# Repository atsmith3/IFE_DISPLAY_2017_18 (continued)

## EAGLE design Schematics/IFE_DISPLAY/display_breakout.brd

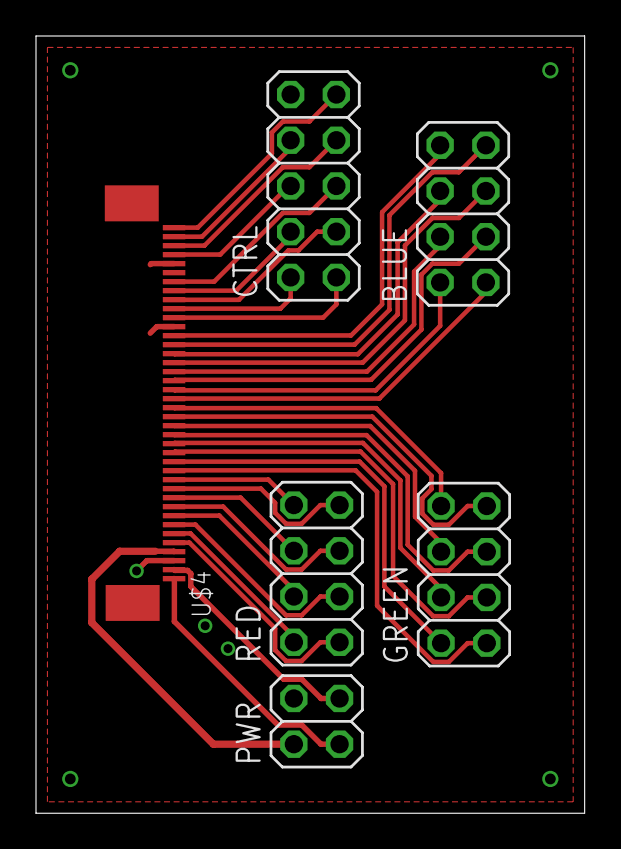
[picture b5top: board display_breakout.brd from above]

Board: 2 copper layers, 30.5 x 43.2 mm, 6 parts (0 on the bottom side), 37 nets.

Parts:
BLUE: 2X04
CTRL: 2X05
GREEN: 2X04
PWR: 2X02
RED: 2X04
U$4: ZIF40_0.5MM_PITCH; ZIF40

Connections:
+3V3: PWR.2, U$4.P$4
BLUE_0: BLUE.1, U$4.P$21
BLUE_1: BLUE.2, U$4.P$22
BLUE_2: BLUE.3, U$4.P$23
BLUE_3: BLUE.4, U$4.P$24
BLUE_4: BLUE.5, U$4.P$25
BLUE_5: BLUE.6, U$4.P$26
BLUE_6: BLUE.7, U$4.P$27
BLUE_7: BLUE.8, U$4.P$28
DISP_CLK: CTRL.1, U$4.P$30
DISP_DEN: CTRL.5, U$4.P$34
DISP_EN: CTRL.2, U$4.P$31
DISP_HSYNC: CTRL.3, U$4.P$32
DISP_LEDA: PWR.3, U$4.P$2
DISP_LEDK: PWR.1, U$4.P$1
DISP_VSYNC: CTRL.4, U$4.P$33
DISP_XL: CTRL.8, U$4.P$39
DISP_XR: CTRL.6, U$4.P$37
DISP_YD: CTRL.7, U$4.P$38
DISP_YU: CTRL.9, U$4.P$40
GND: PWR.4, U$4.P$3, U$4.P$29, U$4.P$36
GREEN_0: GREEN.1, U$4.P$13
GREEN_1: GREEN.2, U$4.P$14
GREEN_2: GREEN.3, U$4.P$15
GREEN_3: GREEN.4, U$4.P$16
GREEN_4: GREEN.5, U$4.P$17
GREEN_5: GREEN.6, U$4.P$18
GREEN_6: GREEN.7, U$4.P$19
GREEN_7: GREEN.8, U$4.P$20
RED_0: RED.1, U$4.P$5
RED_1: RED.2, U$4.P$6
RED_2: RED.3, U$4.P$7
RED_3: RED.4, U$4.P$8
RED_4: RED.5, U$4.P$9
RED_5: RED.6, U$4.P$10
RED_6: RED.7, U$4.P$11
RED_7: RED.8, U$4.P$12

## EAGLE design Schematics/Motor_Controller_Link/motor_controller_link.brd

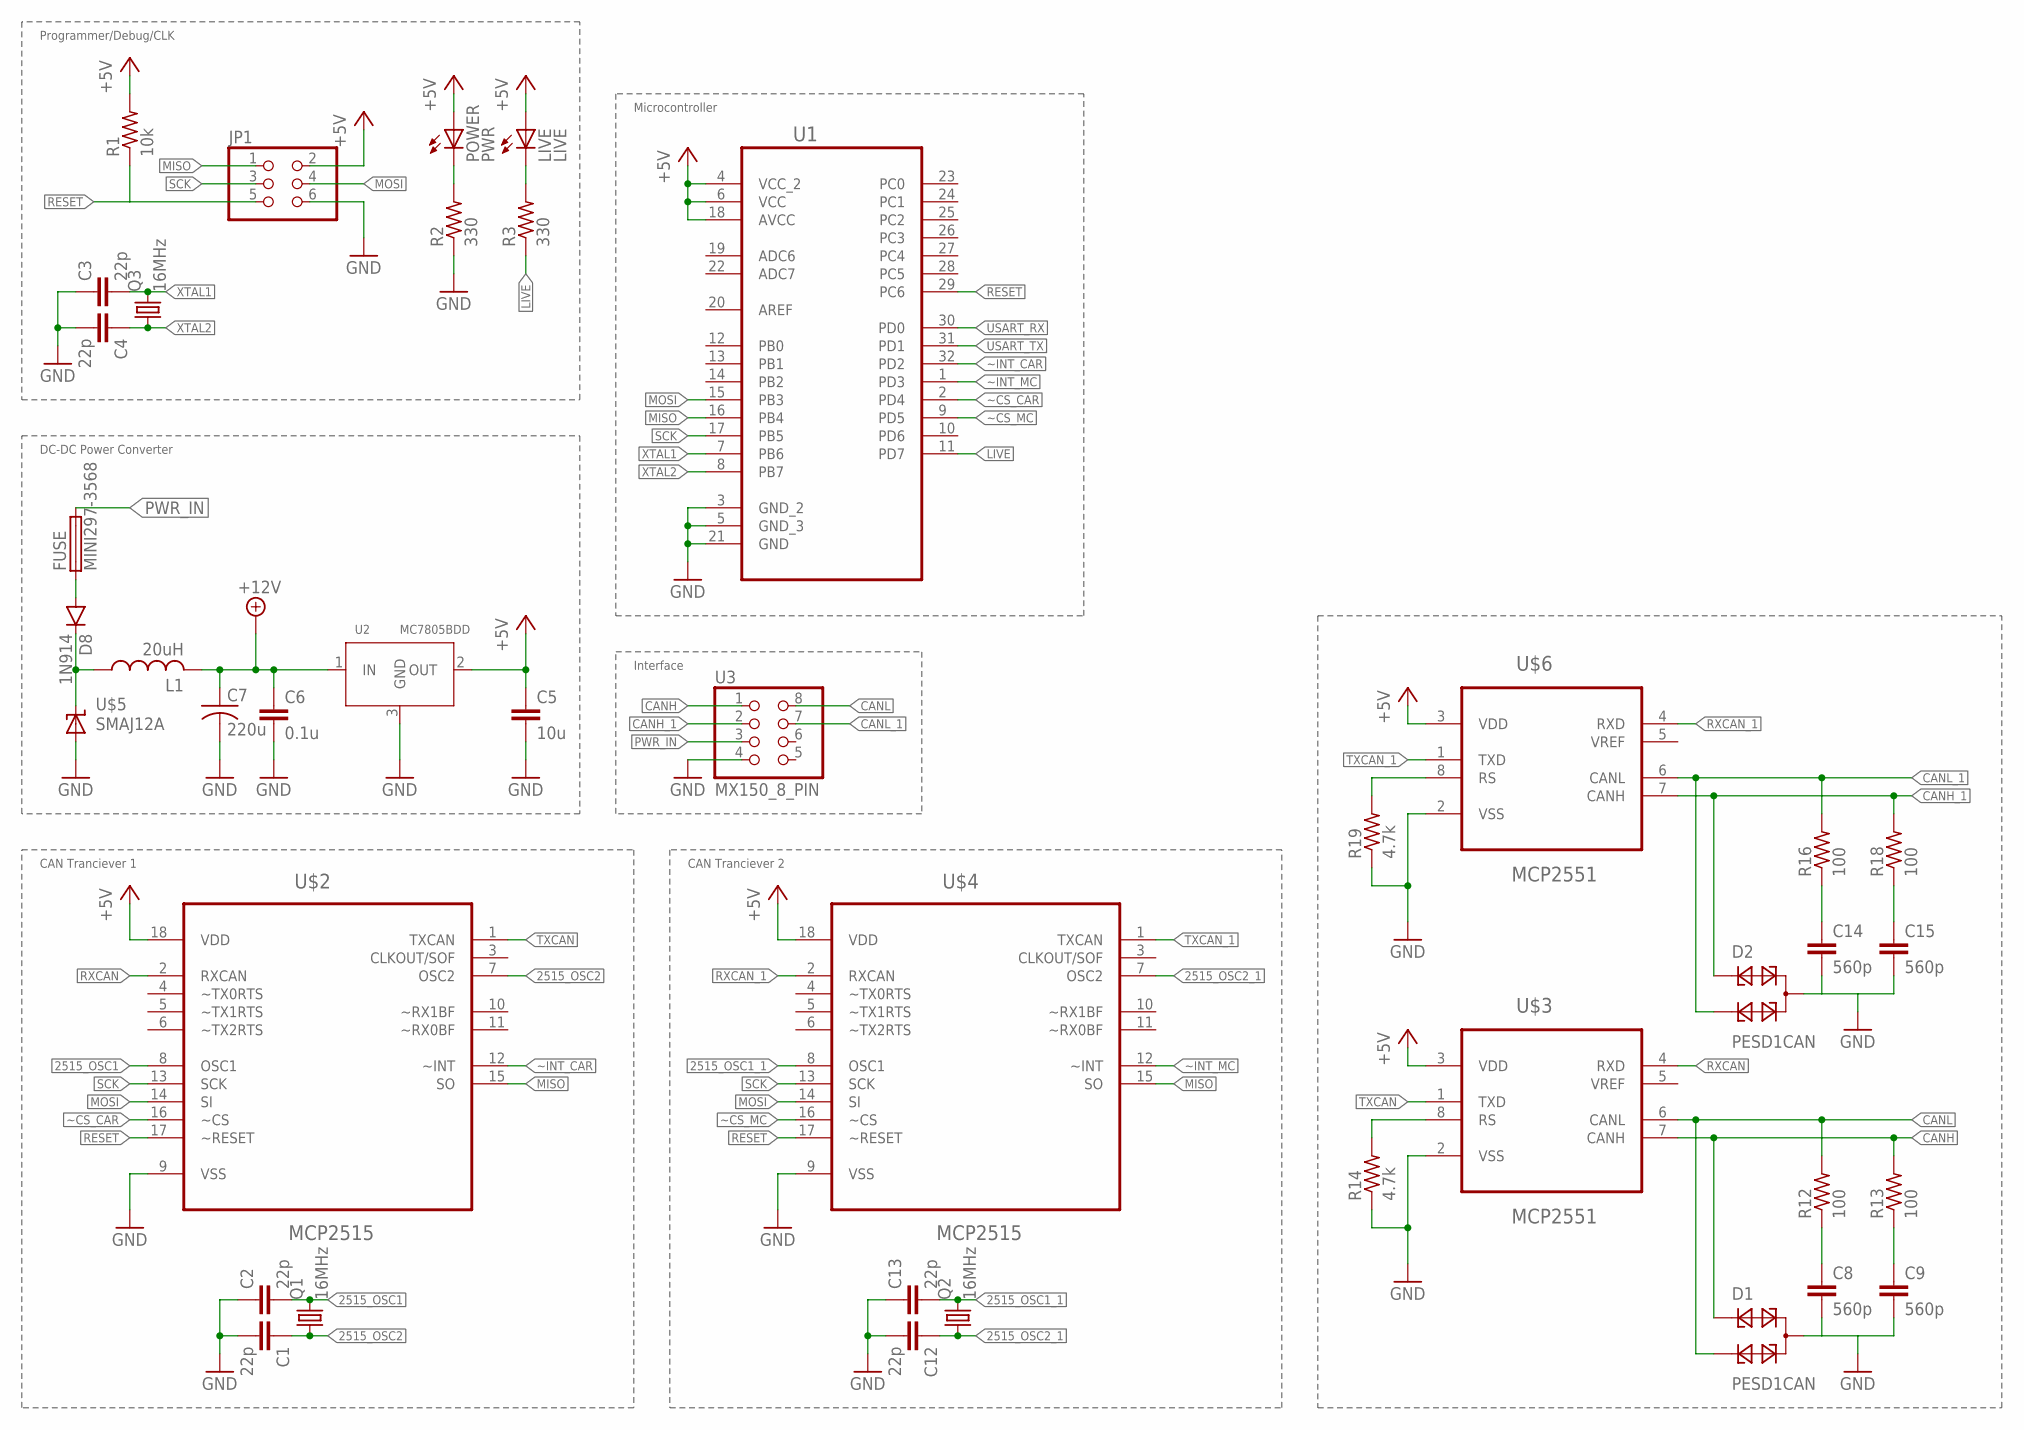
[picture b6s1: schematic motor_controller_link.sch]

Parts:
C1, C2, C3, C4, C12, C13: 22p; C0805K
C5: 10u; C0805K
C6: 0.1u; C0805K
C7: 220u; C1206
C8, C9, C14, C15: 560p; C0805K
D1, D2: PESD1CAN; SOT23
D8: 1N914; SMA-DIODE
FUSE: MINI297-3568; 3568
JP1: PINHD-2X3; 2X03
L1: 20uH; MSS7348
LIVE: LIVE; SML0805
POWER: PWR; SML0805
Q1, Q2, Q3: 16MHz; CTS406
R1: 10k; R0805
R2, R3: 330; R0805
R12, R13, R16, R18: 100; R0805
R14, R19: 4.7k; R0805
U1: ATMEGA328P-AU; QFP80P900X900X120-32N
U2: MC7805BDD; DPAK
U3: MX150_8_PIN; MX150_8
U$2, U$4: MCP2515; SOIC127P1034X264-18N
U$3, U$6: MCP2551; SOIC127P600X175-8N
U$5: SMAJ12A; DO-214AC

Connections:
2515_OSC1: C2.2, Q1.3 (2), U$2.8 (OSC1)
2515_OSC1_1: C13.2, Q2.3 (2), U$4.8 (OSC1)
2515_OSC2: C1.1, Q1.1, U$2.7 (OSC2)
2515_OSC2_1: C12.1, Q2.1, U$4.7 (OSC2)
+5V: C5.1, JP1.2, LIVE.A, POWER.A, R1.2, U1.4 (VCC_2), U1.6 (VCC), U1.18 (AVCC), U2.2 (OUT), U$2.18 (VDD), U$3.3 (VDD), U$4.18 (VDD), U$6.3 (VDD)
+12V: C6.1, C7.1, L1.P$2 (2), U2.1 (IN)
CANH: D1.1, R13.2, U3.1, U$3.7 (CANH)
CANH_1: D2.1, R18.2, U3.2 (3), U$6.7 (CANH)
CANL: D1.2, R12.2, U3.8 (2), U$3.6 (CANL)
CANL_1: D2.2, R16.2, U3.7 (4), U$6.6 (CANL)
GND: C1.2, C2.1, C3.1, C4.2, C5.2, C6.2, C7.2, C8.2, C9.2, C12.2, C13.1, C14.2, C15.2, D1.3, D2.3, JP1.6, R2.1, R14.1, R19.1, U1.3 (GND_2), U1.5 (GND_3), U1.21 (GND), U2.3 (GND), U3.4 (7), U$2.9 (VSS), U$3.2 (VSS), U$4.9 (VSS), U$5.A, U$6.2 (VSS)
LIVE: R3.1, U1.11 (PD7)
MISO: JP1.1, U1.16 (PB4), U$2.15 (SO), U$4.15 (SO)
MOSI: JP1.4, U1.15 (PB3), U$2.14 (SI), U$4.14 (SI)
unnamed: R14.2, U$3.8 (RS)
unnamed: C14.1, R16.1
unnamed: POWER.C, R2.2
unnamed: LIVE.C, R3.2
unnamed: C8.1, R12.1
unnamed: C9.1, R13.1
unnamed: C15.1, R18.1
unnamed: D8.C, L1.P$1 (1), U$5.C
unnamed: R19.2, U$6.8 (RS)
unnamed: D8.A, FUSE.P$1 (1), FUSE.P$4 (1)
PWR_IN: FUSE.P$2 (2), FUSE.P$3 (2), U3.3 (5)
RESET: JP1.5, R1.1, U1.29 (PC6), U$2.17 (~RESET), U$4.17 (~RESET)
RXCAN: U$2.2 (RXCAN), U$3.4 (RXD)
RXCAN_1: U$4.2 (RXCAN), U$6.4 (RXD)
SCK: JP1.3, U1.17 (PB5), U$2.13 (SCK), U$4.13 (SCK)
TXCAN: U$2.1 (TXCAN), U$3.1 (TXD)
TXCAN_1: U$4.1 (TXCAN), U$6.1 (TXD)
USART_RX: U1.30 (PD0)
USART_TX: U1.31 (PD1)
XTAL1: C3.2, Q3.3 (2), U1.7 (PB6)
XTAL2: C4.1, Q3.1, U1.8 (PB7)
~CS_CAR: U1.2 (PD4), U$2.16 (~CS)
~CS_MC: U1.9 (PD5), U$4.16 (~CS)
~INT_CAR: U1.32 (PD2), U$2.12 (~INT)
~INT_MC: U1.1 (PD3), U$4.12 (~INT)

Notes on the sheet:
DC-DC Power Converter
CAN Tranciever 1
CAN Tranciever 2
Programmer/Debug/CLK
Microcontroller
Interface

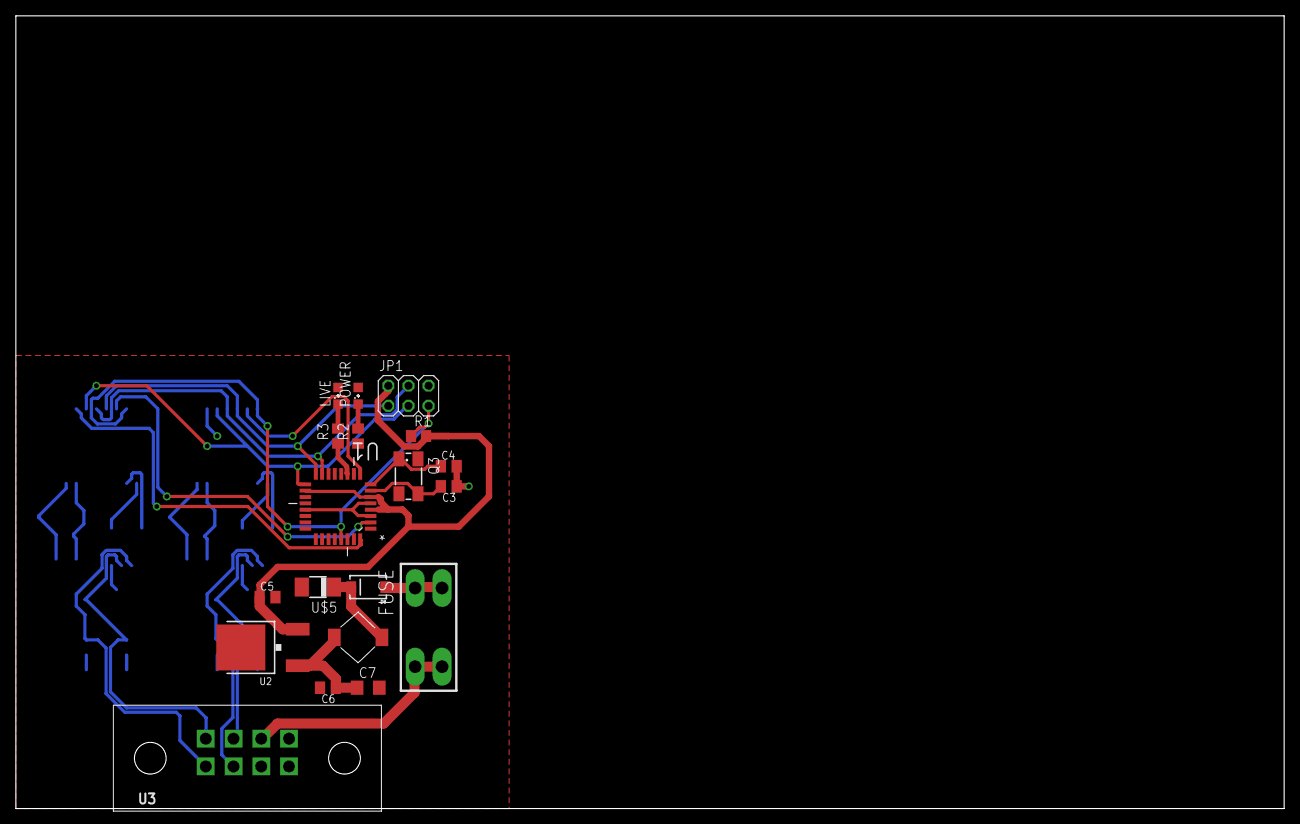
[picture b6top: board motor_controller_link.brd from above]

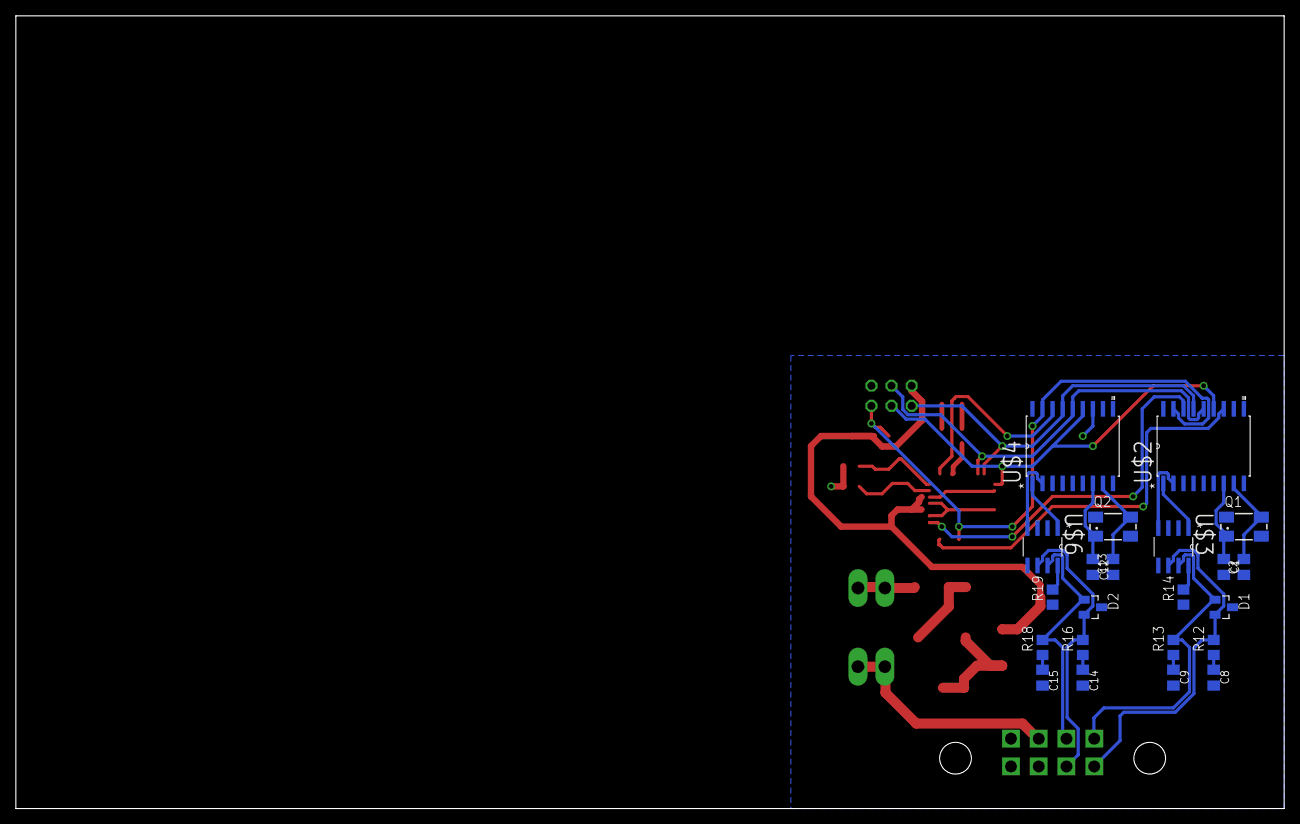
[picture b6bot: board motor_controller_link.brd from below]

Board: 2 copper layers, 160.0 x 100.0 mm, 41 parts (22 on the bottom side), 37 nets.

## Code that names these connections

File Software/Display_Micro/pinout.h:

/*
 * Illini Formula Electric
 * 
 * Dashboard Revision 2 - 2018
 *
 * Pinout
 *
 */

#ifndef _PINOUT_H
#define _PINOUT_H

#define MOSI                        11
#define MISO                        12
#define SCK                         13
#define RXD                         0
#define TXD                         1     
#define CS_CAN                      19    // Chip Select for CAN Module
#define INT_CAN                     2     // Interrupt pin for CAN Module
#define DISPLAY_PWM                 9
#define DEBUG                       10    // Debug LED
//#define CAN_STBY                  9     // CAN Sleep Mode Select (MCP 25625)

/* FPGA INTERFACE */
#define FPGA_D0                     14
#define FPGA_D1                     15
#define FPGA_D2                     16
#define FPGA_D3                     17
#define FPGA_R0                     4
#define FPGA_R1                     5
#define FPGA_R2                     6
#define FPGA_R3                     7
#define FPGA_WRITE                  3
#define FPGA_ADDR                   18

#endif

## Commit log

2017-06-30 Organization
2017-06-30 Adding documentation
2017-06-30 Design Changes
2017-07-07 base FPGA project added
2017-09-08 Finished bootloader circuitry for Cyclone II
2017-09-08 Added Micro programmer circuit
2017-09-15 Updated the Display Design Specification
2017-09-28 Starting Layout of Motor Controller Interface
2017-09-28 Adding projects
2017-09-28 Almost done with initial layout
2017-10-08 More work on Display Schematic
2017-10-09 Figuring out power circuit
2017-10-10 More progress on the schematic
2017-10-15 Started creating the ZIF 40 Pin Connector
2017-10-15 Working on Breakout Board Layout
2017-10-15 Display Breakout Board done
2017-10-16 figuring out DC-DC converters
2017-10-28 DCDC added need to adjust values
2017-10-31 Finalizing Display Schematic
2017-10-31 Initial board organization. Time to route
2017-11-02 Layout started
2017-11-02 Routing and thinking about the FPC connector
2017-11-02 More optimizations and working on interconnect for display board
2017-11-02 Board Complete, DRC Complete, Just have to add Name and IFE Logo
2017-11-03 Finished display board, added IFE BMP and text
2017-11-03 Fixed some random clearance issues
2017-11-05 Finished design v1.0
2017-11-07 Display Driver Working
2017-11-07 Gotta build a C++ program to convert images to text with our color pallate
2017-11-08 rudimentary sprite generator working
2017-11-08 determining colors for palate
2017-11-08 Added Rudimentary support for sprites and color mapper
2017-11-08 Displayed IFE Logo, must work on sprite generator software
2017-11-10 added 120 ohm resistor
2017-12-02 Redid the Switching Supplies
2017-12-11 Added 3d model of board
2017-12-11 Added BOM
2017-12-12 Trying new scalable sprite generator
2017-12-12 Going to generate other scene
2017-12-12 Generated display Render
2017-12-12 Restructuring Memory
2017-12-18 Starting Documentation
2017-12-18 Switching to PC
2017-12-18 Finishing up hardware portion of report
2017-12-21 Almost done with Report
2018-01-17 Resized Vias
2018-01-23 Documentation
2018-02-05 Adding New Part
2018-02-13 Changes to Serial Config Device
2018-02-15 Adding cyclone 10 devices for version2
2018-02-15 Added Serial config flash for cyclone 10
2018-02-15 adding linear regs
2018-02-15 Created Linear Regulators
2018-02-16 Working on adding 2.5V for the PLL
2018-02-16 Creating 2.5V reg
2018-02-16 New 2.5V reg
2018-02-16 Finished power dist - Working on optimizing connections to FPGA
2018-02-17 General Layout
2018-02-17 Need to fix oscillators, Initial placement done
2018-02-17 Updted Oscillators, routing ~60%
2018-02-17 Finished Routing, Adding LOGO
2018-02-19 Cleaning up the aesthetic
2018-02-19 Fixing Aesthetic ~ 50% COmplete
2018-02-20 Getting board size down on X axis so it is cheaper
2018-02-20 Fixed board sizeing for cost efficiency + Aesthetic
2018-02-21 Added gerbers
2018-02-22 Added new CAN Chips
2018-02-23 Made LED Driver Test Circuit
2018-02-25 Added New Relay
2018-03-07 Working on Shutdown Documentation
2018-03-27 Added new parts
2018-03-27 Made a few custom parts
2018-04-11 Added new devices
2018-04-11 Got sprite gen working
2018-04-15 Programmed ATmega328p on V2.0
2018-04-16 Added Parts
2018-04-16 Testing Cyclone 10 programming
2018-04-17 Some Software Work
2018-04-19 Working on R3
2018-04-19 V3 Under Review
2018-04-19 Reviewed and Ordered V3
2018-04-23 About to generate sprites
2018-04-23 added sprites
2018-04-23 Display Output Set Up
2018-04-25 Generating Johns Sprites
2018-04-25 Made text and sprite module
2018-04-25 Creating packman and ghosts
2018-04-25 Creating Sprites
2018-04-25 Added pac.bmp
2018-04-25 Generated pac
2018-04-29 Created red ghost
2018-04-29 Finishing sprites
2018-04-29 Finished Sprites
2018-04-29 Generating track for packman
2018-04-29 added track
2018-04-30 Finishing Tracks
2018-04-30 Made new tracks
2018-04-30 Done
2018-04-30 Jk not done just making Johns win screens
2018-04-30 More Sprites
2018-04-30 blegh
2018-05-30 Merging
2018-06-01 Adding more PMIC
2018-06-04 More Display Microcontroller + More components in Library
2018-06-05 Display v4 - What should have been done all along
2018-06-06 Display v4 - Routing
2018-06-06 Display v4 - ready to autoroute
2018-06-06 Display v4 - autorouted
2018-06-06 Display v4 - Adding FTDI for ease of programming
2018-06-07 v4 Ready to be printed
2018-07-30 Added 2 new power relays
2018-07-31 Added SPST Relay
2018-08-01 Added New ST Lib
2018-08-03 MFG Organied Libraries
2018-08-04 More tidying up
2018-08-13 Added Microchip Library
2018-09-18 Created new parts
2018-09-22 More parts
2018-11-03 Adding new STM Parts
2018-11-03 Updating libs
2018-11-04 Updating Molex Libraries
2018-11-04 Updating parts libraries
2020-01-12 Adding the sample code for the FPGA board
